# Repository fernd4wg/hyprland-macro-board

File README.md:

# Hyprland Macro Board
  A fully custom macro board designed to improve workflow on Hyprland or any related window managers.

# LCD Image Help
  It might be that you do not like the images I've used for the LCD Screen (in hyprland-macro-board/macro-board-images/). If that is the case I would recommend using https://javl.github.io/image2cpp/ to 
convert images. You can make your own 128x32 (recommended) or get images off the internet and have image2cpp monochrome and resize them for you.

# Copying Keyboard Firmware to qmk_firmware Directory 
  Copy /hyprland-macro-board/hyprmacroboard into where your qmk_firmware/keyboards directory is so you can easily flash the firmware. Do this in the /hypr-macro-board directory

``` 
cp hyprmacroboard /PATH/TO/YOUR/QMK/KEYBOARD/DIR
```

# Compiling and Flashing
* Compile and Flash Firmware:
``` 
qmk compile -kb hyprmacroboard -km default
```

# Things to know 
  Resetting the board is annoying 9_9. All the components that are not the switches do not fit into their respective places so do not print the case parts until this message is not in this file.

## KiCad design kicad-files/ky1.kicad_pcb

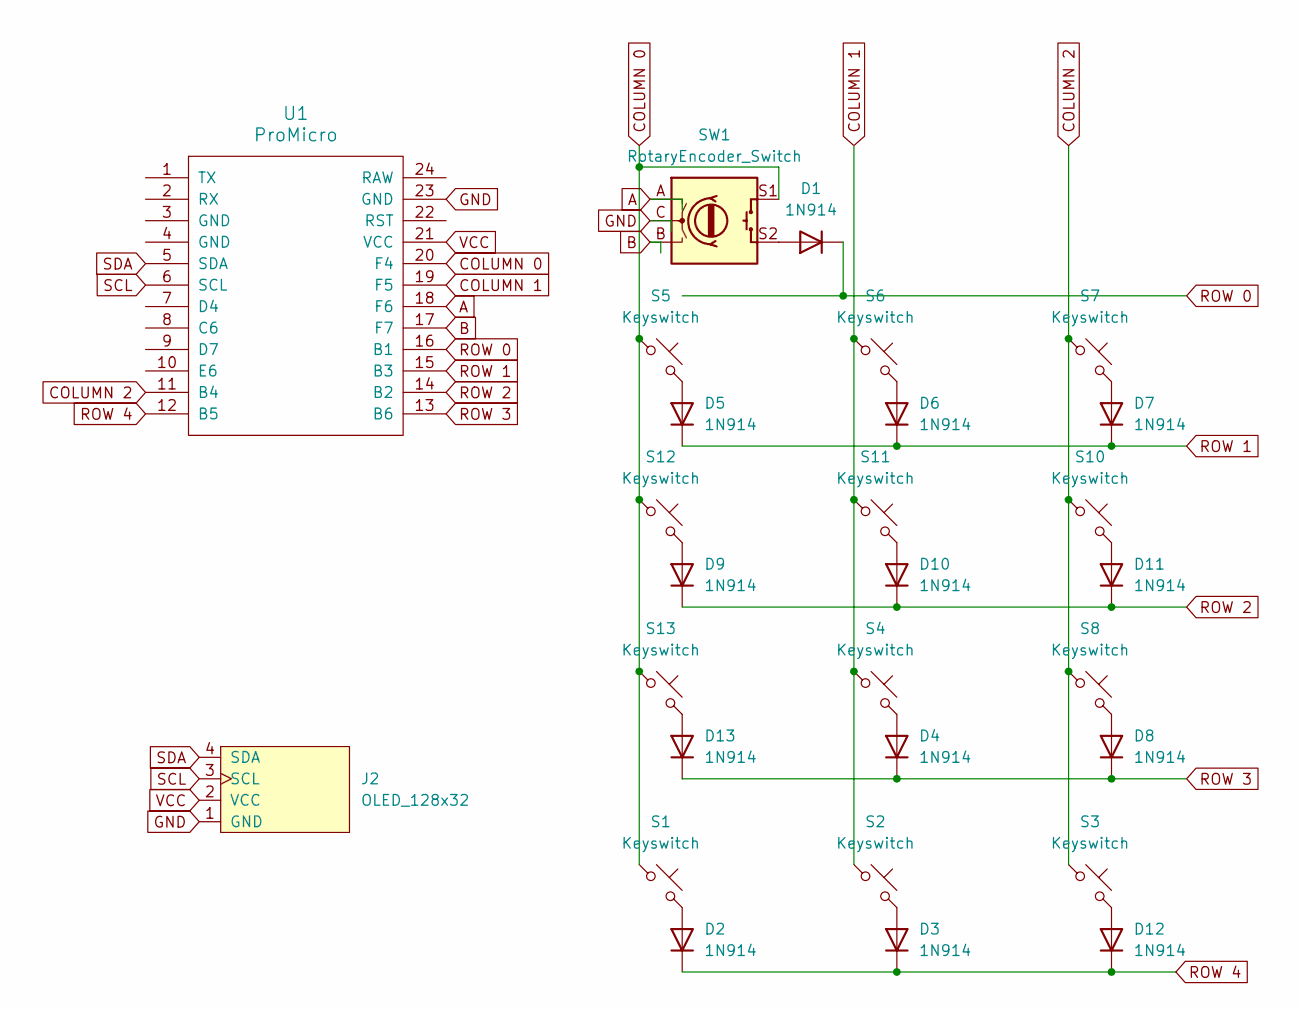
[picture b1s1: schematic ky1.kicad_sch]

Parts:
D1, D2, D3, D4, D5, D6, D7, D8, D9, D10, D11, D12, D13: 1N914; D_DO-35_SOD27_P7.62mm_Horizontal
J2: OLED_128x32
S1, S2, S3, S4, S5, S6, S7, S8, S10, S11, S12, S13: Keyswitch; SW_Cherry_MX_PCB_1.00u
SW1: RotaryEncoder_Switch; RotaryEncoder_Alps_EC11E-Switch_Vertical_H20mm
U1: ProMicro; ProMicro-EnforcedTop

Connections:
A: SW1.A, U1.18 (F6)
B: SW1.B, U1.17 (F7)
COLUMN 0: S1.1, S5.1, S12.1, S13.1, SW1.S1, U1.20 (F4)
COLUMN 1: S2.1, S4.1, S6.1, S11.1, U1.19 (F5)
COLUMN 2: S3.1, S7.1, S8.1, S10.1, U1.11 (B4)
GND: J2.1 (GND), SW1.C, U1.23 (GND)
unnamed: D1.2 (A), SW1.S2
unnamed: D2.2 (A), S1.2
unnamed: D3.2 (A), S2.2
unnamed: D4.2 (A), S4.2
unnamed: D5.2 (A), S5.2
unnamed: D6.2 (A), S6.2
unnamed: D7.2 (A), S7.2
unnamed: D8.2 (A), S8.2
unnamed: D9.2 (A), S12.2
unnamed: D10.2 (A), S11.2
unnamed: D11.2 (A), S10.2
unnamed: D12.2 (A), S3.2
unnamed: D13.2 (A), S13.2
ROW 0: D1.1 (K), U1.16 (B1)
ROW 1: D5.1 (K), D6.1 (K), D7.1 (K), U1.15 (B3)
ROW 2: D9.1 (K), D10.1 (K), D11.1 (K), U1.14 (B2)
ROW 3: D4.1 (K), D8.1 (K), D13.1 (K), U1.13 (B6)
ROW 4: D2.1 (K), D3.1 (K), D12.1 (K), U1.12 (B5)
SCL: J2.3 (SCL), U1.6 (SCL)
SDA: J2.4 (SDA), U1.5 (SDA)
VCC: J2.2 (VCC), U1.21 (VCC)

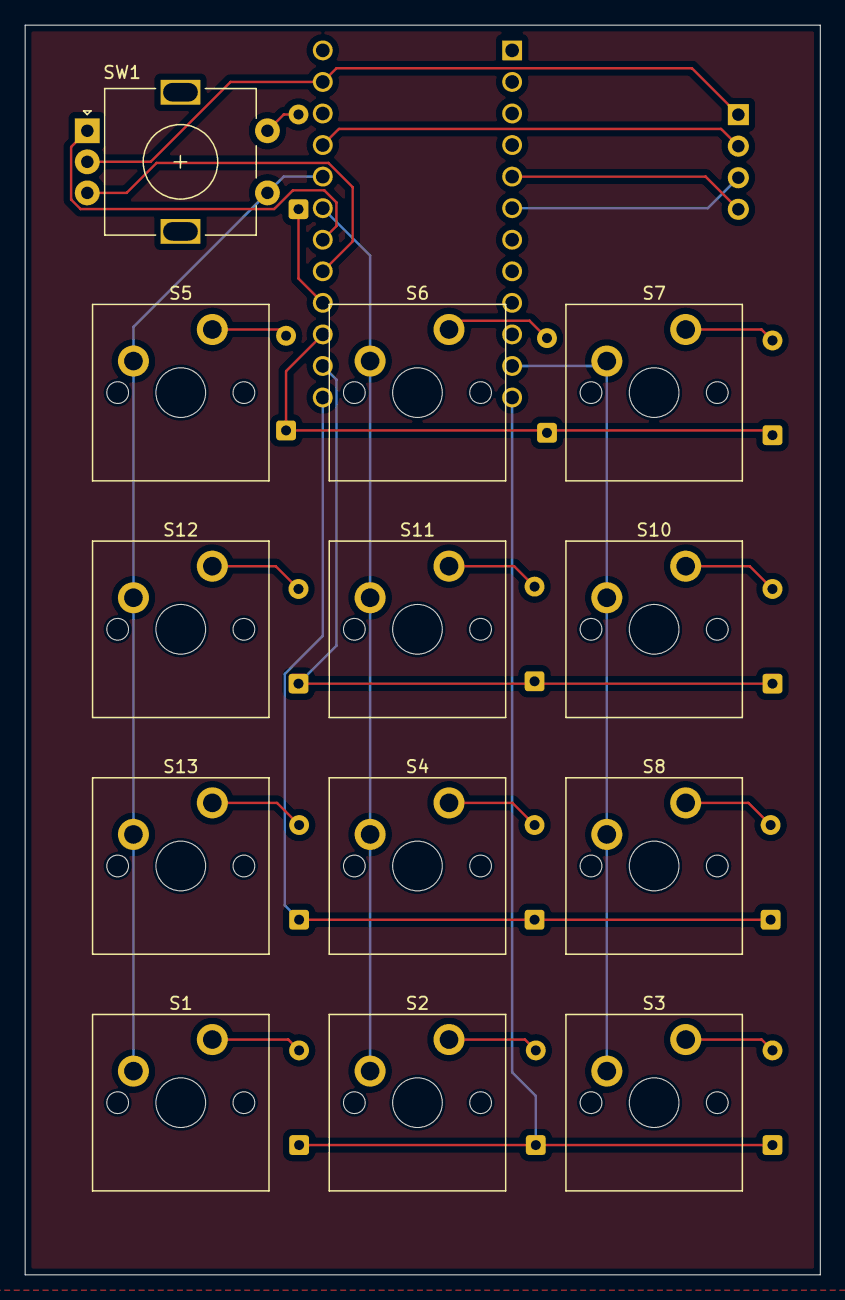
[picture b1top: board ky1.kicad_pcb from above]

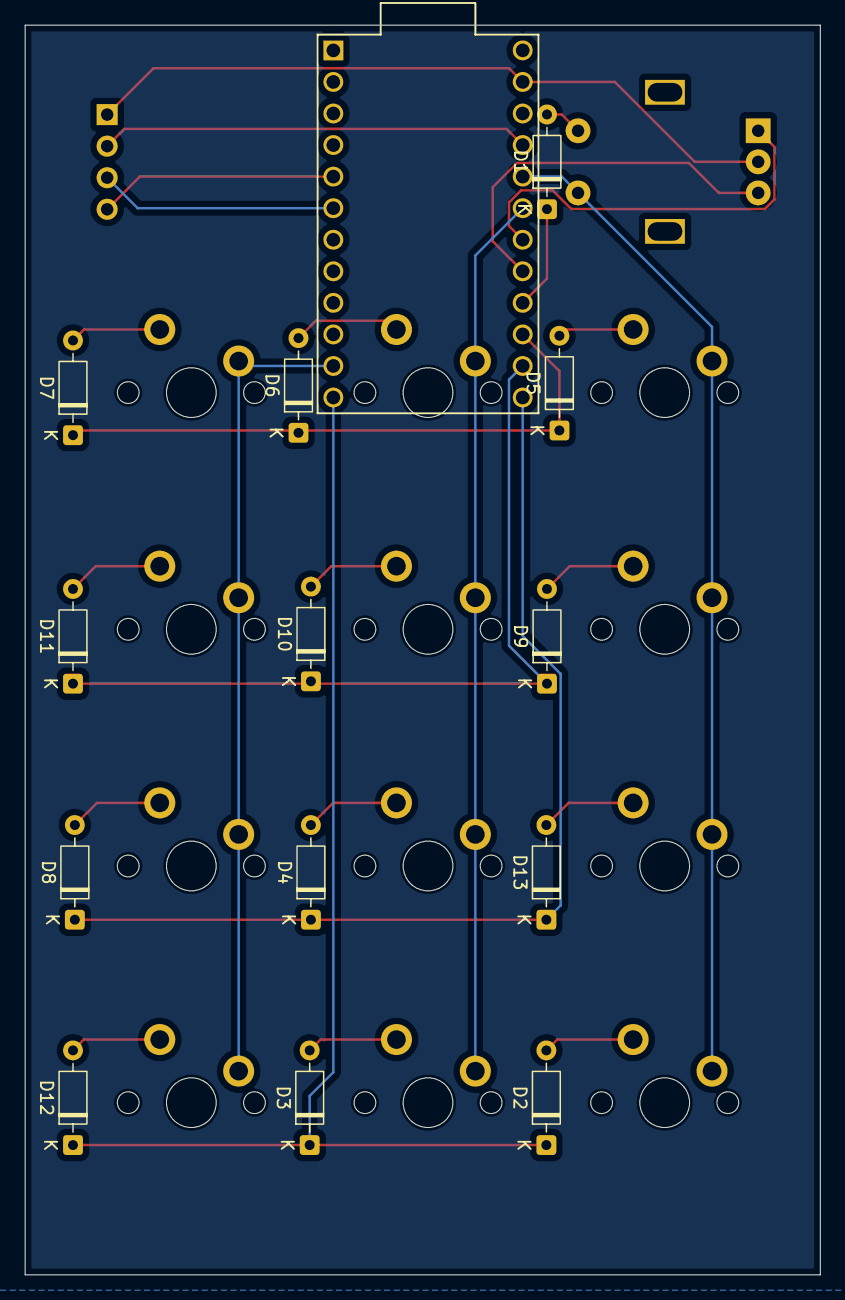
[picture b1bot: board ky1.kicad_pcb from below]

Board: 2 copper layers, 64.0 x 100.6 mm, 28 parts (14 on the bottom side), 27 nets.

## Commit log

2025-07-18 Adding first batch of files that I've used thus far
2025-07-29 Adding 1st Batch of QMK Firmware Files
2025-08-01 Adding updates to keymap.c
2025-08-01 Updating manufacturer
2025-08-03 Savepoint!
2025-08-11 deleting old qmk-firmware
2025-08-11 adding new qmk-firmware
